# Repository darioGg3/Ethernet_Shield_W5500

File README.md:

# Ethernet_Shield_W5500

PCB SPI - Ethernet Shield basado en el integrado W5500 de Wiznet.

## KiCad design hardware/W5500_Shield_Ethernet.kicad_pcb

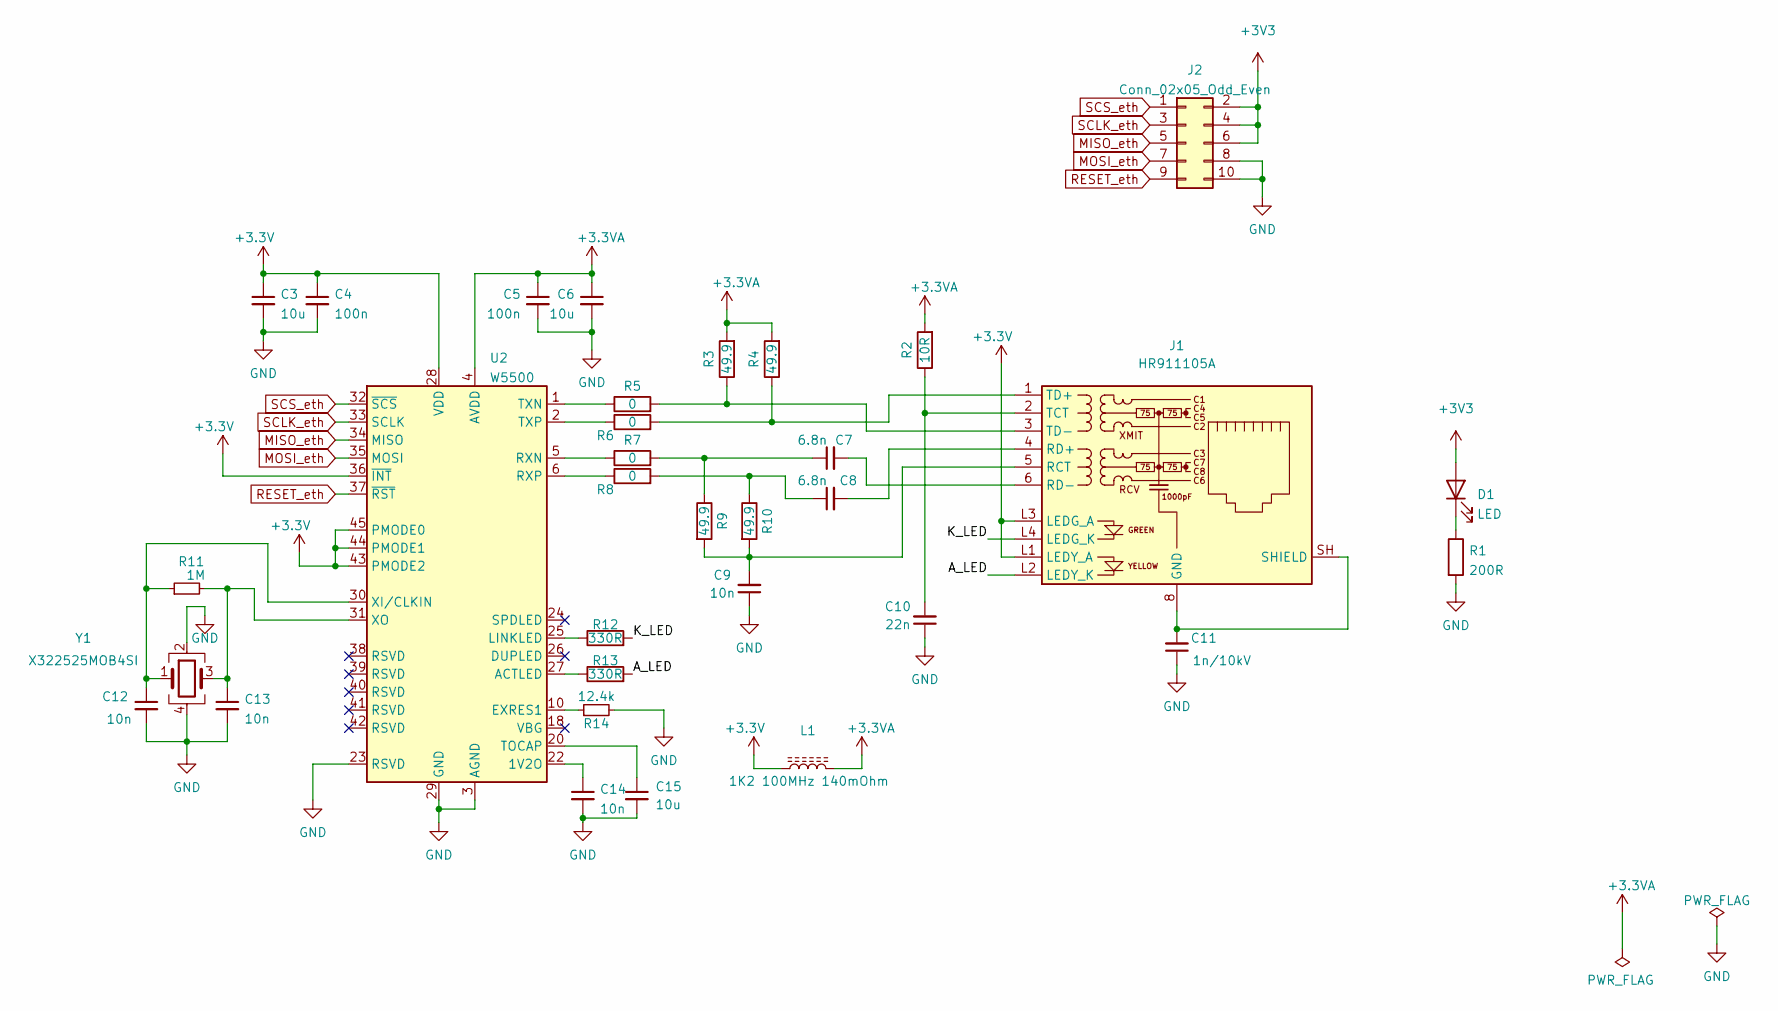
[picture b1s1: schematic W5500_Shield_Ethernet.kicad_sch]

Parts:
C3, C6, C15: 10u; C_0402_1005Metric
C4, C5: 100n; C_0402_1005Metric
C7, C8: 6.8n; C_0402_1005Metric
C9, C12, C13, C14: 10n; C_0402_1005Metric
C10: 22n; C_0402_1005Metric
C11: 1n/10kV; C_1206_3216Metric
D1: LED; LED_0805_2012Metric
J1: HR911105A; RJ45_Bel_SI-60062-F
J2: Conn_02x05_Odd_Even; PinSocket_2x05_P2.54mm_Vertical
L1: 1K2 100MHz 140mOhm; L_0603_1608Metric
R1: 200R; R_0603_1608Metric
R2: 10R; R_0402_1005Metric
R3, R4, R9, R10: 49.9; R_0402_1005Metric
R5, R6, R7, R8: 0; R_0402_1005Metric
R11: 1M; R_0402_1005Metric
R12, R13: 330R; R_0402_1005Metric
R14: 12.4k; R_0402_1005Metric
U2: W5500; LQFP-48_7x7mm_P0.5mm
Y1: X322525MOB4SI; Crystal_SMD_3225-4Pin_3.2x2.5mm

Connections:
+3.3VA: C5.1, C6.1, L1.2, R2.2, R3.2, R4.2, U2.4 (AVDD), U2.8 (AVDD), U2.11 (AVDD), U2.15 (AVDD), U2.17 (AVDD), U2.21 (AVDD)
/A_LED: J1.L2 (LEDY_K), R13.2
/K_LED: J1.L4 (LEDG_K), R12.2
GND: C3.2, C4.2, C5.2, C6.2, C9.1, C10.1, C11.1, C12.2, C13.2, C14.2, C15.2, J2.8, J2.10, R1.2, R14.2, U2.3 (AGND), U2.9 (AGND), U2.14 (AGND), U2.16 (AGND), U2.19 (AGND), U2.23 (RSVD), U2.29 (GND), U2.48 (AGND), Y1.2, Y1.4
MISO_eth: J2.5, U2.34 (MISO)
MOSI_eth: J2.7, U2.35 (MOSI)
unnamed: C7.1, R7.2, R9.1
unnamed: C7.2, J1.6 (RD-)
unnamed: C8.1, R8.2, R10.1
unnamed: C8.2, J1.4 (RD+)
unnamed: C9.2, J1.5 (RCT), R9.2, R10.2
unnamed: C10.2, J1.2 (TCT), R2.1
unnamed: C11.2, J1.8 (GND), J1.SH (SHIELD)
unnamed: C12.1, R11.1, U2.30 (XI/CLKIN), Y1.1
unnamed: C13.1, R11.2, U2.31 (XO), Y1.3
unnamed: C14.1, U2.22 (1V2O)
unnamed: C15.1, U2.20 (TOCAP)
unnamed: D1.1 (K), R1.1
unnamed: J1.1 (TD+), R4.1, R6.2
unnamed: J1.3 (TD-), R3.1, R5.2
unnamed: R5.1, U2.1 (TXN)
unnamed: R6.1, U2.2 (TXP)
unnamed: R7.1, U2.5 (RXN)
unnamed: R8.1, U2.6 (RXP)
unnamed: R12.1, U2.25 (LINKLED)
unnamed: R13.1, U2.27 (ACTLED)
unnamed: R14.1, U2.10 (EXRES1)
RESET_eth: J2.9, U2.37 (~RST)
SCLK_eth: J2.3, U2.33 (SCLK)
SCS_eth: J2.1, U2.32 (~SCS)

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
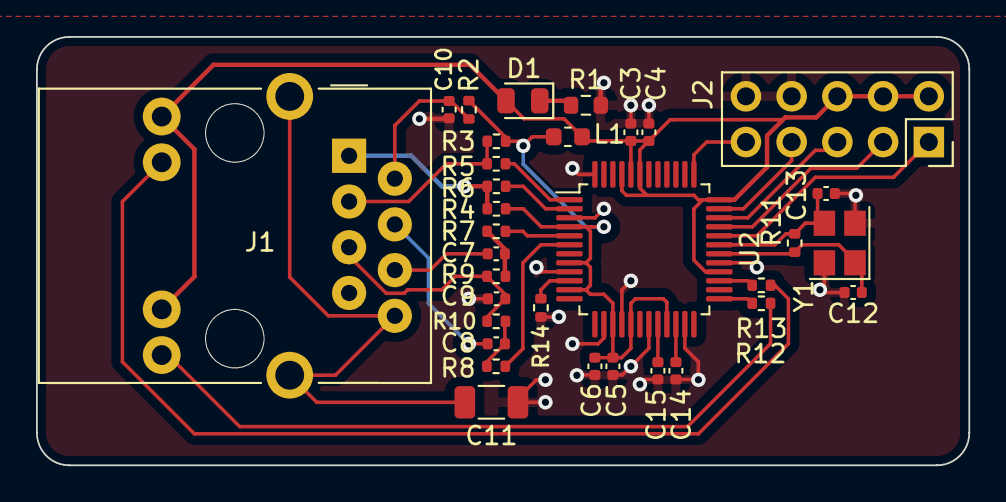
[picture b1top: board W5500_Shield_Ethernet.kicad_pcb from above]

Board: 2 copper layers, 51.8 x 23.8 mm, 33 parts (0 on the bottom side), 31 nets.

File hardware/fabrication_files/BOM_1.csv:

"Id","Designator","Footprint","Quantity","Comment","Supplier and ref",
1,"Y1","Crystal_SMD_3225-4Pin_3.2x2.5mm",1,"X322525MOB4SI",,,
2,"C13,C14,C12,C9","C_0402_1005Metric",4,"10n",,,
3,"C10","C_0402_1005Metric",1,"22n",,,
4,"R12,R13","R_0402_1005Metric",2,"330R",,,
5,"R11","R_0402_1005Metric",1,"1M",,,
6,"C8,C7","C_0402_1005Metric",2,"6.8n",,,
7,"L1","L_0603_1608Metric",1,"1K2 100MHz 140mOhm",,,
8,"R10,R4,R9,R3","R_0402_1005Metric",4,"49.9",,,
9,"C11","C_1206_3216Metric",1,"1n/10kV",,,
10,"U2","LQFP-48_7x7mm_P0.5mm",1,"W5500",,,
11,"R7,R6,R8,R5","R_0402_1005Metric",4,"0",,,
12,"C15,C3,C6","C_0402_1005Metric",3,"10u",,,
15,"D1","LED_0805_2012Metric",1,"LED",,,
16,"C4,C5","C_0402_1005Metric",2,"100n",,,
17,"R14","R_0402_1005Metric",1,"12.4k",,,
18,"R1","R_0603_1608Metric",1,"200R",,,
19,"R2","R_0402_1005Metric",1,"10R",,,

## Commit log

2022-04-14 Listo para enviar a jlcpcb
2022-04-15 schematics and photos
2022-04-15 deleting some fabrication_files
2022-06-14 RSVD pins
    Estaban conectados a gnd y se dejaron al aire como indica el datasheet
2022-06-15 Preparado para enviar a farbricar
    Listo el BOM
    Listo el POS
    añadido script python para facilitar
    comprobado en JLC pero no enviado a fabricar
2022-07-21 added some examples schematic
